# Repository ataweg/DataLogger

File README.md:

# DataLogger
DataLogger using "Arduino UNO" board and Greiman SdFat library

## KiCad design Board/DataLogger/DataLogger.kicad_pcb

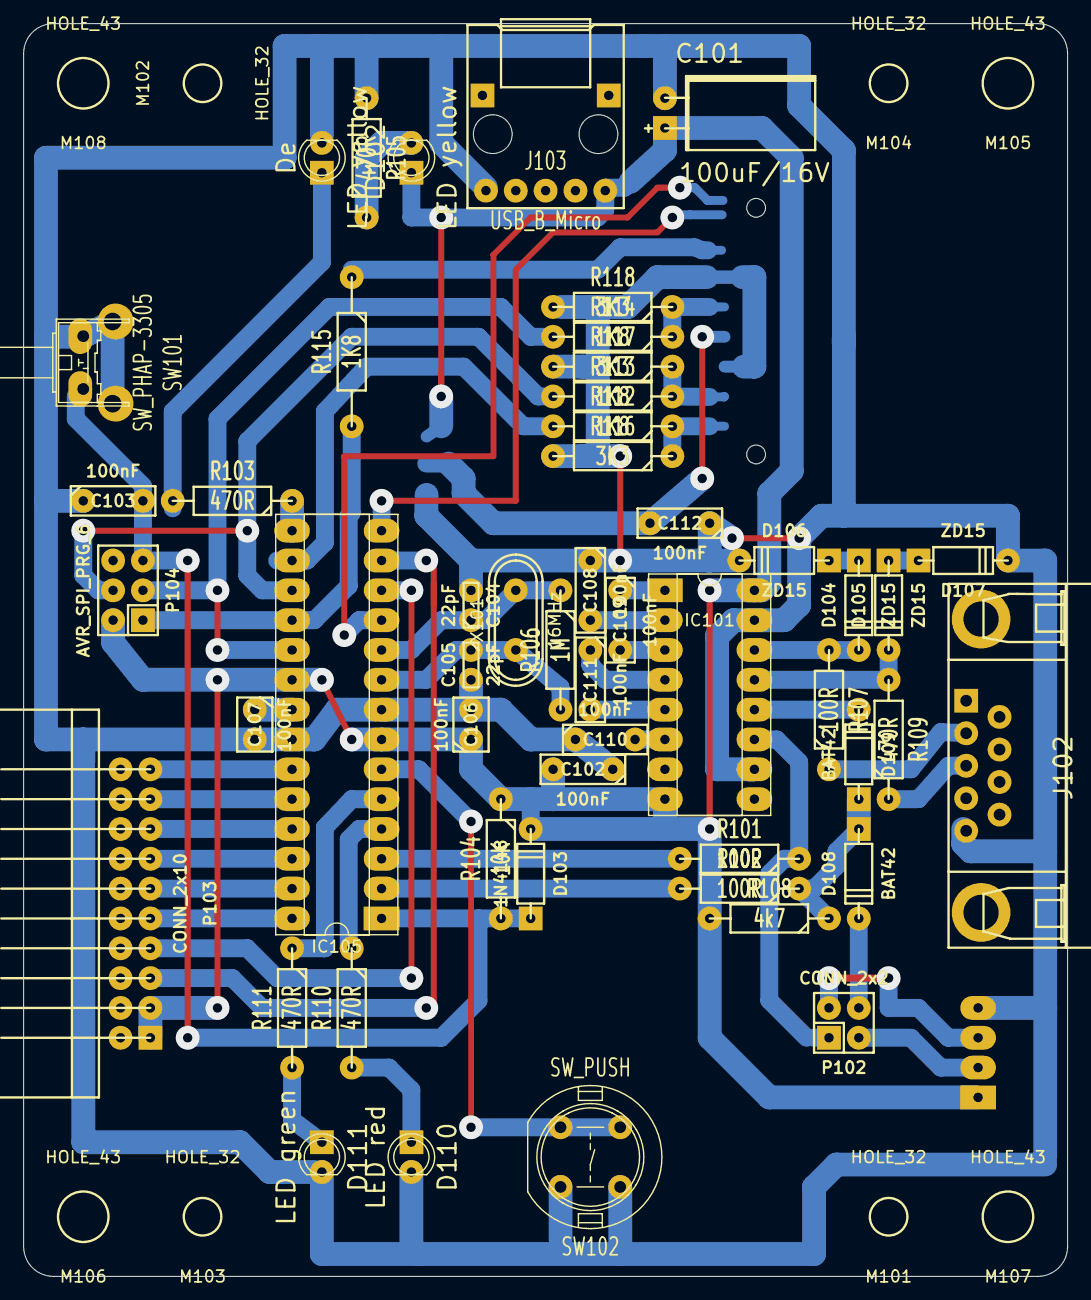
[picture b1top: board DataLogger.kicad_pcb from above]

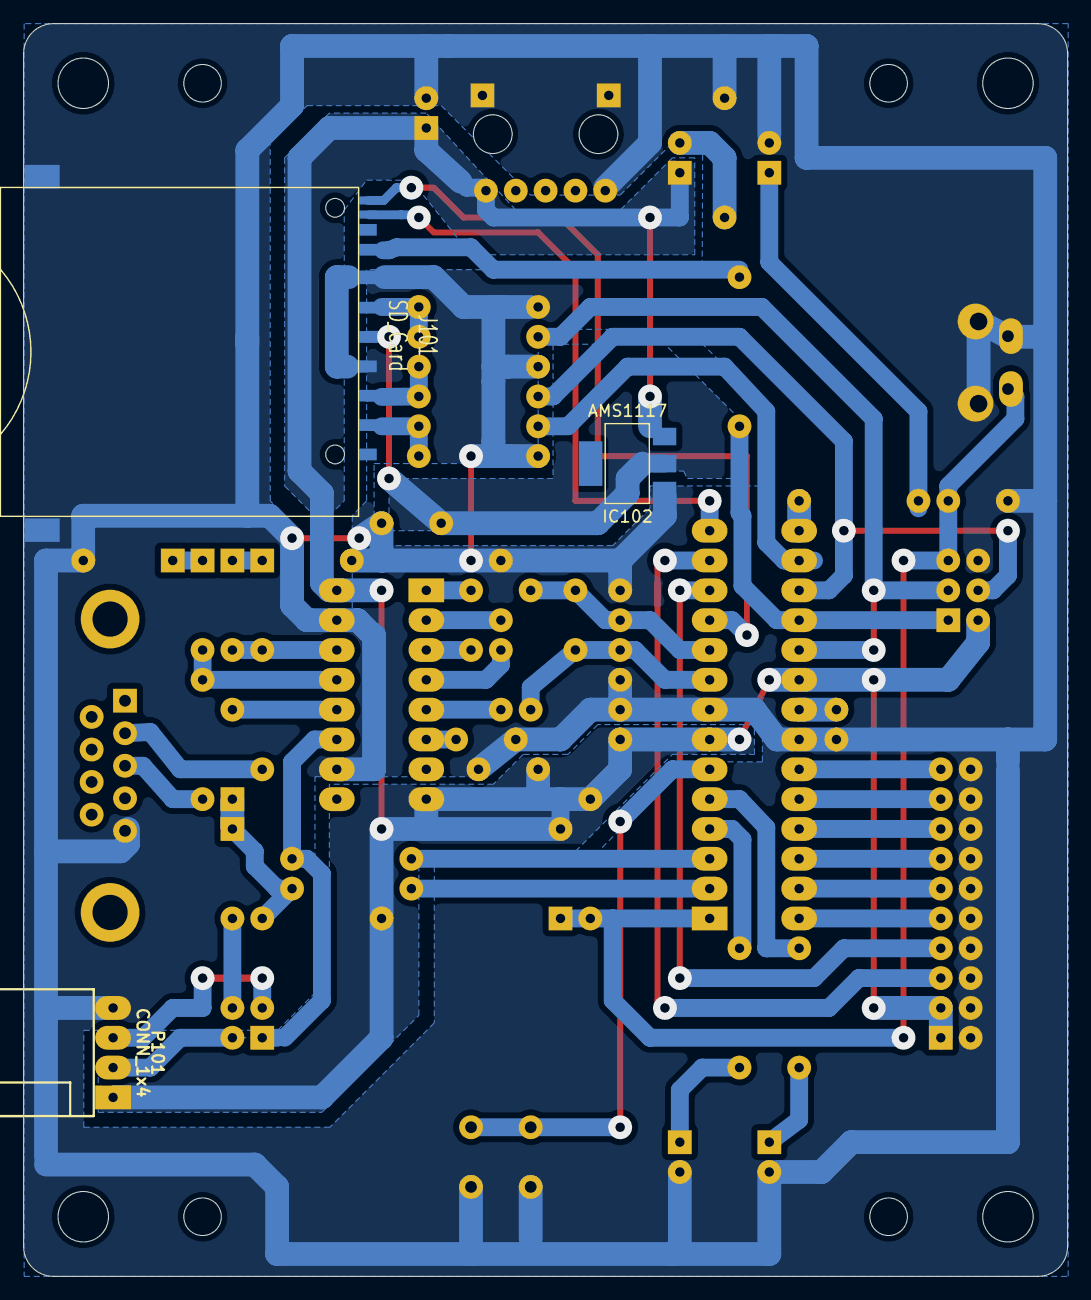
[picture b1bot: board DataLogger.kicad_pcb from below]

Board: 2 copper layers, 88.9 x 106.7 mm, 62 parts (3 on the bottom side), 53 nets.

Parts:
C101: 100uF/16V; CP1HR_6.3x11
C102, C103, C108, C109, C110, C111, C112: 100nF; C2_WIMA_2.5x6.5
C104, C105: 22pF; C1D3_CER
C106, C107: 100nF; C1_WIMA_3x7.5
D102: LED yellow; LED_3mm_yellow
D103: 1N4148; D3
D104, D105, D106, D107: ZD15; D3
D108, D109: BAT42; D3
D110: LED red; LED_3mm_red
D111: LED green; LED_3mm_green
De: LED yellow; LED_3mm_yellow
IC101: MAX3232; Socket_DIP-16_W7.62mm
IC102: AMS1117; SOT-223
IC105: ATmega328P-PU; Socket_DIP-28_W7.62mm
J101: SD_Card; SdCard_RSMT2MQ
J102: SUBD-F09C-US; DB9FC_US
J103: USB_B_Micro; USB-Micro-Connector
M101, M102, M103, M104: HOLE_32
M105, M106, M107, M108: HOLE_43
P101: CONN_1x4; pinsocket_90_1x4
P102: CONN_2x2; pinheader_2x2
P103: CONN_2x10; box_pinheader_90_2x10
P104: AVR_SPI_PRG_6; pinheader_2x3
R101, R102, R107: 100R; R4
R103, R105, R109, R110, R111: 470R; R4
R104: 10K; R4
R106: 1M; R4
R108: 4k7; R4
R112, R113, R114: 1K8; R4
R115: 1K8; R4-5
R116, R117, R118: 3K3; R4
SW101: SW_PHAP-3305; PHAP-3305B-8.35mm
SW102: SW_PUSH; DT6-grey
X101: 16MHz; HC-49SV

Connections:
+3.3V: C112.2, IC102.2, J101.4
+5V: C101.1, C102.2, C106.1, D102.1, D103.2, IC101.8, IC101.16, IC102.3, IC105.7, IC105.20, J103.1, P101.1, P103.1, P103.3, P104.2, R104.1, R108.2
/AREF: C107.1, IC105.21
/BTN: IC105.6, SW102.1
/CD: IC105.14, J101.10
/CS: IC105.16, R112.2
/DEBUG_LED: IC105.15, R103.1
/LED_R: IC105.4, R110.1
/LEG_G: IC105.5, R111.1
/MISO: IC105.18, P104.1, R115.2
/MOSI: IC105.17, P104.4, R113.2
/PC0: IC105.23, P103.19
/PC1: IC105.24, P103.17
/PC2: IC105.25, P103.15
/PC3: IC105.26, P103.13
/PC4: IC105.27, P103.11
/PC5: IC105.28, P103.9
/PD6: IC105.12, P103.7
/PD7: IC105.13, P103.5
/RESET: C103.2, D103.1, IC105.1, P104.5, R104.2, SW101.1
/RX: J102.3, R109.1
/RXD: IC105.2, R102.2
/RX_OUT: D109.2, IC101.12
/RX_TTL: P101.2, P102.3
/SCK: IC105.19, P104.3, R114.2
/TX: J102.2, R107.1
/TXD: IC105.3, R101.2
/TX_IN: IC101.11, P102.1, R101.1
/TX_TTL: P101.3, P102.2
/WP: IC105.11, J101.11
/XTAL1: C105.1, IC105.9, R106.2, X101.2
/XTAL2: C104.1, IC105.10, R106.1, X101.1
GND: C101.2, C102.1, C103.1, C104.2, C105.2, C106.2, C107.2, C108.1, C110.1, C112.1, D106.2, D107.2, D110.2, D111.2, De.2, IC101.10, IC101.15, IC102.1, IC105.8, IC105.22, J101.3, J101.6, J101.12, J101.13, J102.5, J103.5, J103.6, P101.4, P103.2, P103.4, P103.6, P103.8, P103.10, P103.12, P103.14, P103.16, P103.18, P103.20, P104.6, R105.2, R116.2, R117.2, R118.2, SW101.2, SW101.3, SW101.4, SW102.2
unnamed: C108.2, IC101.2
unnamed: C109.1, IC101.1
unnamed: C109.2, IC101.3
unnamed: C110.2, IC101.6
unnamed: C111.1, IC101.4
unnamed: C111.2, IC101.5
unnamed: De.1, R103.2
unnamed: D102.2, R105.1
unnamed: D104.1, D106.1
unnamed: D104.2, IC101.14, R107.2
unnamed: D105.1, D107.1
unnamed: D105.2, IC101.13, R109.2
unnamed: D108.1, D109.1, R102.1, R108.1
unnamed: D108.2, P102.4
unnamed: D110.1, R110.2
unnamed: D111.1, R111.2
unnamed: J101.1, R112.1, R116.1
unnamed: J101.2, R113.1, R117.1
unnamed: J101.5, R114.1, R118.1
unnamed: J101.7, R115.1

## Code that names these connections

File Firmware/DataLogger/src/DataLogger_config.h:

// --------------------------------------------------------------------------
//
// 2020-05-25  AWe   adapted for use in DataLogger project
// 2019-02-13  AWe   Pin D10 cannot used as input
//                   see C:\Program Files (x86)\Arduino\hardware\arduino\avr\libraries\SPI\src\SPI.cpp(47):
//
// --------------------------------------------------------------------------

// --------------------------------------------------------------------------
//
// MIT License
//
// Copyright (c) 2021 Axel Werner (ataweg)
//
// Permission is hereby granted, free of charge, to any person obtaining a copy
// of this software and associated documentation files (the "Software"), to deal
// in the Software without restriction, including without limitation the rights
// to use, copy, modify, merge, publish, distribute, sublicense, and/or sell
// copies of the Software, and to permit persons to whom the Software is
// furnished to do so, subject to the following conditions:
//
// The above copyright notice and this permission notice shall be included in all
// copies or substantial portions of the Software.
//
// THE SOFTWARE IS PROVIDED "AS IS", WITHOUT WARRANTY OF ANY KIND, EXPRESS OR
// IMPLIED, INCLUDING BUT NOT LIMITED TO THE WARRANTIES OF MERCHANTABILITY,
// FITNESS FOR A PARTICULAR PURPOSE AND NONINFRINGEMENT. IN NO EVENT SHALL THE
// AUTHORS OR COPYRIGHT HOLDERS BE LIABLE FOR ANY CLAIM, DAMAGES OR OTHER
// LIABILITY, WHETHER IN AN ACTION OF CONTRACT, TORT OR OTHERWISE, ARISING FROM,
// OUT OF OR IN CONNECTION WITH THE SOFTWARE OR THE USE OR OTHER DEALINGS IN THE
// SOFTWARE.
// --------------------------------------------------------------------------

#ifndef __DATALOGGER_CONFIG_H__
#define __DATALOGGER_CONFIG_H__

#include "PinNames.h"      // PinName

// --------------------------------------------------------------------------
//
// --------------------------------------------------------------------------

// #define ARDUINO_UNO_REV3
#define EVAL_BREADBOARD

// serial output requires 1,816 kB flash memory
#define USE_SERIAL_OUTPUT

// --------------------------------------------------------------------------

// LED_BUILDIN defineid in ...\avr\variants\standard\pins_arduino.h

#if defined( ARDUINO_UNO_REV3 )
   // Arduino UNO rev3
   #define DEBUG_LED             LED_BUILTIN       // normally pin D13 (SCK)
#elif defined( EVAL_BREADBOARD )
   // arduino uno rev3 with breadborad
   #define DEBUG_LED             D9
#else
   // atmega318p breadboard
   #define DEBUG_LED             D4
#endif

// --------------------------------------------------------------------------

#if defined( ARDUINO_UNO_REV3 )

   #define BTN_Pin               NC       // n.c.

   #define LED_R_Pin             NC       // n.c.
   #define LED_G_Pin             NC       // n.c.

   #define OSZI_YELLOW_Pin       NC       // n.c.
   #define OSZI_BLUE_Pin         NC       // n.c.
   #define OSZI_RED_Pin          NC       // n.c.
   #define OSZI_GREEN_Pin        NC       // n.c.

   // pins for sdcard connector
   #define SS_Pin                SS       // pin 10
   #define CD_Pin                NC       // Card Detect
   #define WP_Pin                NC       // Write Protect

#elif defined( EVAL_BREADBOARD )

   #define BTN_Pin               D4

   #define LED_R_Pin             D2
   #define LED_G_Pin             D3

 #if ( LOG_LOCAL_LEVEL >= LOG_DEBUG )
   #define OSZI_YELLOW_Pin       A0
   #define OSZI_BLUE_Pin         A1
   #define OSZI_RED_Pin          A2
   #define OSZI_GREEN_Pin        A3
 #else
   #define OSZI_YELLOW_Pin       NC       // n.c.
   #define OSZI_BLUE_Pin         NC       // n.c.
   #define OSZI_RED_Pin          NC       // n.c.
   #define OSZI_GREEN_Pin        NC       // n.c.
 #endif

   // pins for sdcard connector
   #define SS_Pin                D10
   #define CD_Pin                D8       // Card Detect
   #define WP_Pin                D5       // Write Protect
#endif

// --------------------------------------------------------------------------
// Timer 2 configuration
// --------------------------------------------------------------------------

#define CPU_FREQUENCY      16000000L      // 16MHz
#define TIMER2_PRESCALER   1024
#define LEDS_UPDATE_RATE   100            // 100HZ - 10ms
#define TIMER2_DIVIDER     ( F_CPU/TIMER2_PRESCALER/LEDS_UPDATE_RATE + 1)

#define TIMER2_RELOAD      ( 256 - TIMER2_DIVIDER )

// --------------------------------------------------------------------------
//
// --------------------------------------------------------------------------
#endif // __DATALOGGER_CONFIG_H__
